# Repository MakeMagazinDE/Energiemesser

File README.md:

Maker Media GmbH

***

# Vom Energiemesser zum Smart Meter

### Wir verwandeln einen geeichten Energie- und Leistungsmesser in ein Smart Meter für Wallboxen und Wärmepumpen.

In PV-Anlagen mit Batteriespeicher lassen sich vorhandene Verbrauchsmesser mit wenig Aufwand als Smart Meter nutzen. Wir verwandeln einen geeichten Energie- und Leistungsmesser mit RS484-Schnittstelle und Modbus-RTU-Protokoll in ein Smart Meter für Wallboxen und Wärmepumpen und zeigen, wie man es im WLAN einbindet und die Verbrauchsdaten im Webbrowser ausgibt.

Den vollständigen Artikel mit der Bauanleitung gibt es in der [Make-Ausgabe 1/25 ab Seite 108](https://www.heise.de/select/make/2025/1/2501015555220177543). Hier finden Sie Listings und Zusatzinfos zum Beitrag.

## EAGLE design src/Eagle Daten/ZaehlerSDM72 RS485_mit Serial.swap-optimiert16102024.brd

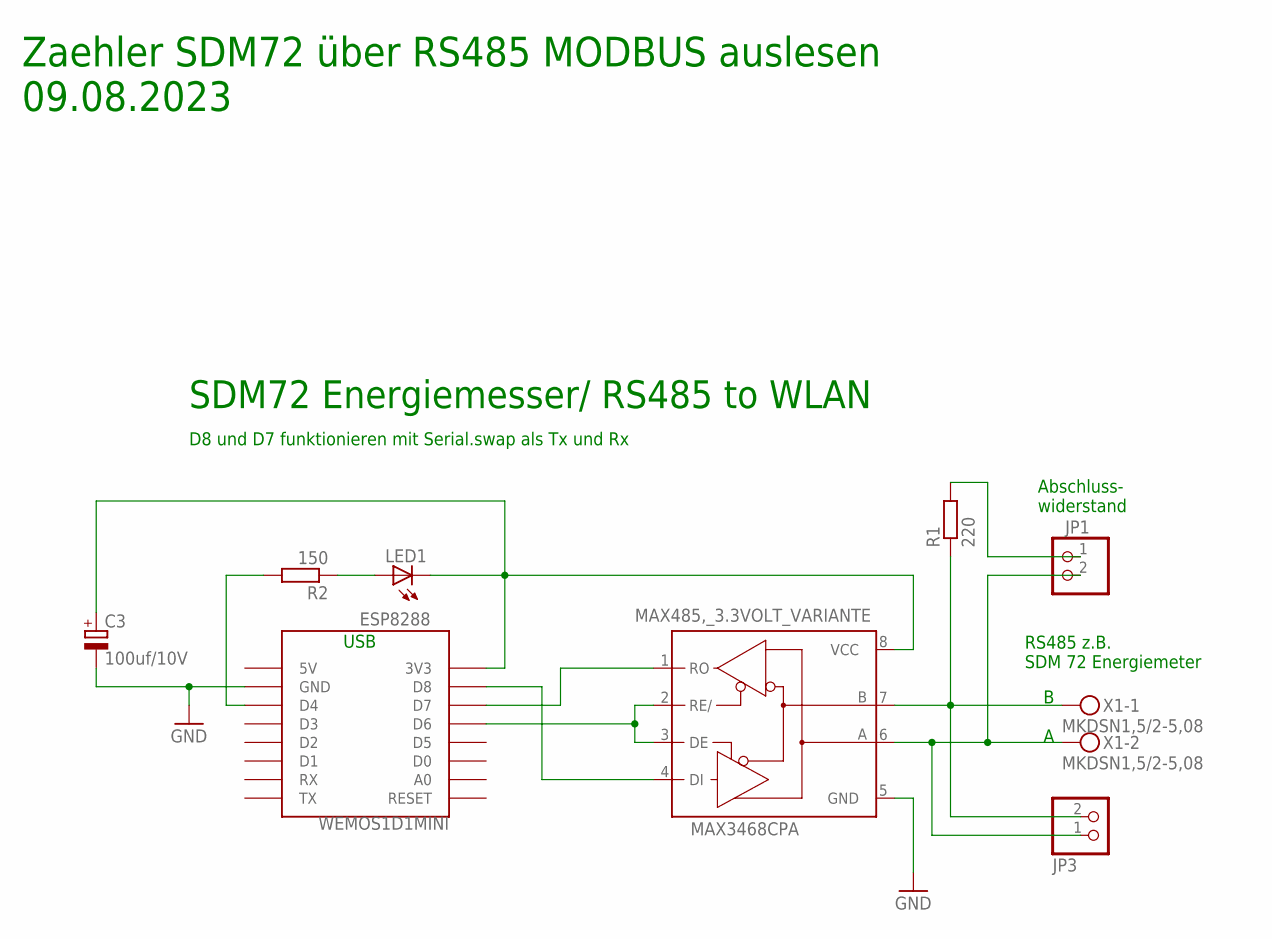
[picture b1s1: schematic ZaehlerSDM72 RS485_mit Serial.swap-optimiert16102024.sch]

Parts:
C3: 100uf/10V; E2,5-7
JP1, JP3: PINHD-1X2/90; 1X02/90
LED1: LED_ELD260; LED_LD260
MAX485,_3.3VOLT_VARIANTE: MAX3468CPA; DIL08
R1: 220; 0207/5V
R2: 150; 0207/5V
WEMOS1D1MINI: ESP8288; WEMOS-D1-MINI
X1: MKDSN1,5/2-5,08

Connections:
GND: C3.-, MAX485,_3.3VOLT_VARIANTE.5 (GND), WEMOS1D1MINI.GND
unnamed: MAX485,_3.3VOLT_VARIANTE.2 (RE/), MAX485,_3.3VOLT_VARIANTE.3 (DE), WEMOS1D1MINI.D6
unnamed: JP1.1, R1.2
unnamed: MAX485,_3.3VOLT_VARIANTE.1 (RO), WEMOS1D1MINI.D7
unnamed: MAX485,_3.3VOLT_VARIANTE.4 (DI), WEMOS1D1MINI.D8
unnamed: R2.2, WEMOS1D1MINI.D4
unnamed: LED1.A, R2.1
unnamed: C3.+, LED1.K (C), MAX485,_3.3VOLT_VARIANTE.8 (VCC), WEMOS1D1MINI.3V3
unnamed: JP3.2, MAX485,_3.3VOLT_VARIANTE.7 (B), R1.1, X1.1
unnamed: JP1.2, JP3.1, MAX485,_3.3VOLT_VARIANTE.6 (A), X1.2

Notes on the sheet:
Zaehler SDM72 über RS485 MODBUS auslesen 09.08.2023
B A
RS485 z.B. SDM 72 Energiemeter
SDM72 Energiemesser/ RS485 to WLAN
Abschluss- widerstand
USB
D8 und D7 funktionieren mit Serial.swap als Tx und Rx

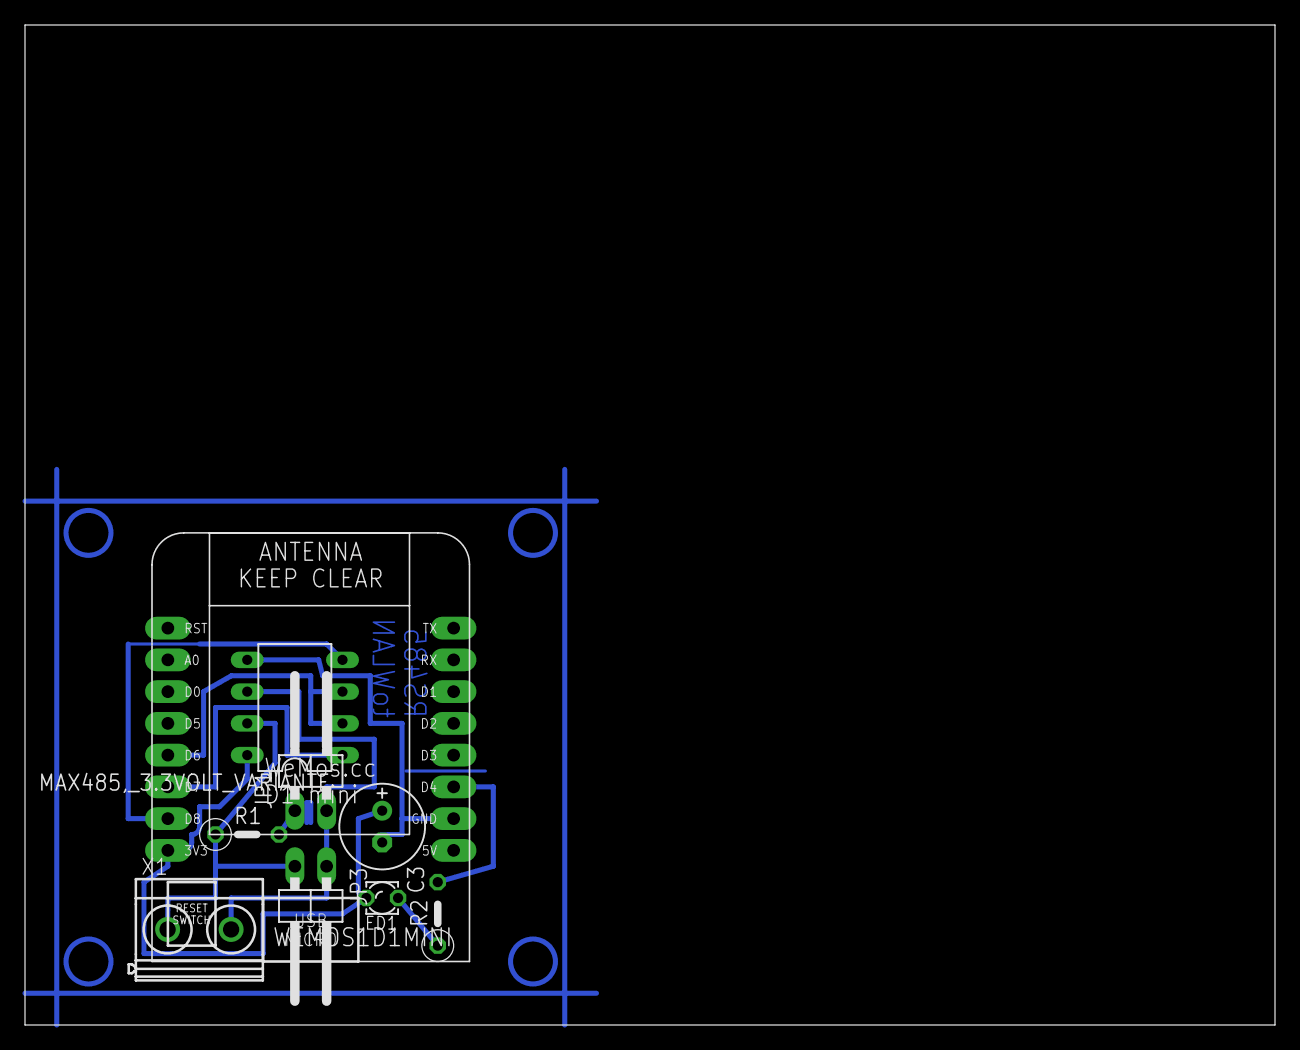
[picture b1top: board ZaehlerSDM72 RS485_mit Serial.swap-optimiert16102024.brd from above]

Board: 2 copper layers, 100.0 x 80.0 mm, 9 parts (0 on the bottom side), 10 nets.

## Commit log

2025-01-28 Create src
2025-01-28 Update src
2025-01-28 Create test
2025-01-28 Create tst
